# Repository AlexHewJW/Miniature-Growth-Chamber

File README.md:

# Miniature-Growth-Chamber
This is an electronics project that aims to create a miniaturised version of growth chamber to cultivate Arabidopsis under microscope under a long period of time. The problem reseachers have is the grow light that the plants need would interfere with some microscope such as the Raman microscope which is supposed to work without any surrounding light interference.

Hence, the project is aim-ed to create a 'light tight' microchamber that is small enough to fit under the microscope while also provide appropriate grow light to cultivate plants.

During my research, I've found out the LEDs would dissipate some heat that can be unconfortable for the plant, which leads me to create a novel solution prototype that uses fibre optic end glow light pipe to transfer light from remotely located LEDs.

Yet, I still continued my research on the original method of installing LEDs inside the growth chamber and found out that the heat dissipation isn't bad at all.

Here you would see 2 EAGLE files for PCB design, which are for both novel and original solution. 

The single AutoCAD file holds the microchamber design for both novel and original solution.

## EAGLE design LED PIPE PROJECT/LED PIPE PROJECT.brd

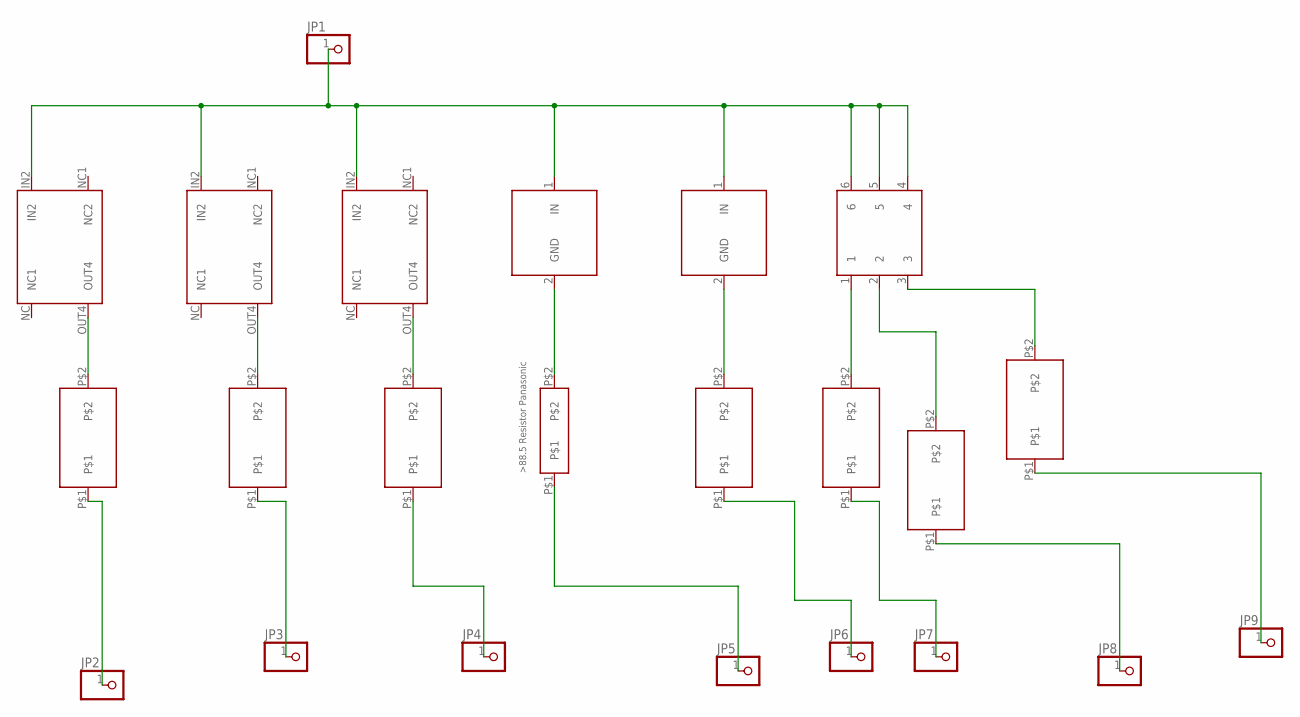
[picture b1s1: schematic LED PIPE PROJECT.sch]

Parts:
JP1, JP2, JP3, JP4, JP5, JP6, JP7, JP8, JP9: PINHD-1X1; 1X01
U$1: UV_LED
U$2: IR_LED
U$3: SMALL_RGB
U$4, U$5, U$6: SMALL_BRIGHT_COOL_WHITE
U$7, U$8, U$9, U$11, U$12, U$13, U$14: 68_60_56_RESISTOR_VISHAY
U$10: 88.5_RESISTOR_PANASONIC; 88.7_RESISTOR_PANASONIC

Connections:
unnamed: JP1.1, U$1.1 (IN), U$2.1 (IN), U$3.4, U$3.5, U$3.6, U$4.IN2, U$5.IN2, U$6.IN2
unnamed: U$6.OUT4, U$7.P$2
unnamed: U$5.OUT4, U$8.P$2
unnamed: U$4.OUT4, U$9.P$2
unnamed: U$1.2 (GND), U$10.P$2
unnamed: U$2.2 (GND), U$11.P$2
unnamed: U$3.1, U$12.P$2
unnamed: U$3.2, U$13.P$2
unnamed: U$3.3, U$14.P$2
unnamed: JP2.1, U$7.P$1
unnamed: JP3.1, U$8.P$1
unnamed: JP4.1, U$9.P$1
unnamed: JP5.1, U$10.P$1
unnamed: JP6.1, U$11.P$1
unnamed: JP7.1, U$12.P$1
unnamed: JP8.1, U$13.P$1
unnamed: JP9.1, U$14.P$1

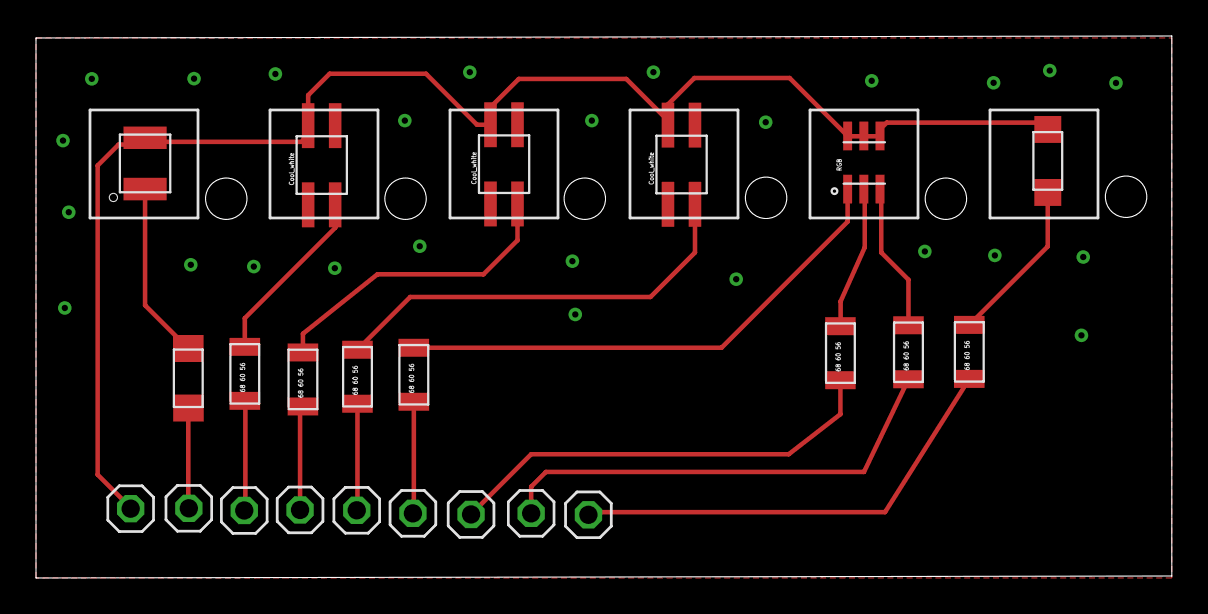
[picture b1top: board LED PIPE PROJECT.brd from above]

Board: 2 copper layers, 63.1 x 30.1 mm, 23 parts (0 on the bottom side), 17 nets.

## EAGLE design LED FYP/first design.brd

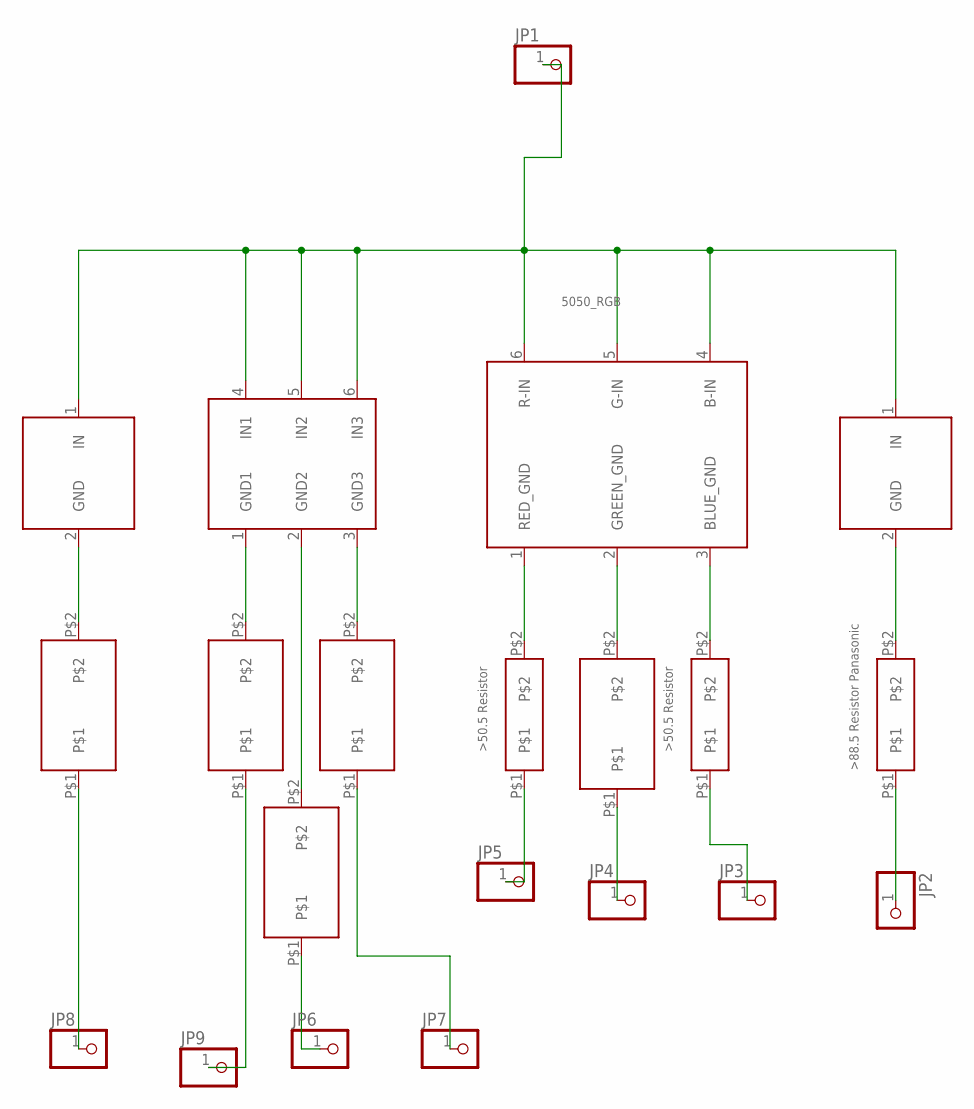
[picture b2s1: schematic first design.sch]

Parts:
JP1, JP2, JP3, JP4, JP5, JP6, JP7, JP8, JP9: PINHD-1X1; 1X01
U$1: 5.0X5.0_WHITE_LED; COOLWHITE5050LED
U$2: 5050_RGB_LED; RGB5050LED
U$3: IR_LED
U$4: UV_LED
U$5: 88.5_RESISTOR_PANASONIC; 88.7_RESISTOR_PANASONIC
U$6, U$7, U$8, U$9, U$12: 68_60_56_RESISTOR_VISHAY
U$10, U$11: 50.5_RESISTOR_TT

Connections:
unnamed: U$1.3 (GND3), U$9.P$2
unnamed: U$1.2 (GND2), U$8.P$2
unnamed: U$1.1 (GND1), U$7.P$2
unnamed: U$3.2 (GND), U$6.P$2
unnamed: U$2.1 (RED_GND), U$10.P$2
unnamed: U$2.2 (GREEN_GND), U$12.P$2
unnamed: U$2.3 (BLUE_GND), U$11.P$2
unnamed: U$4.2 (GND), U$5.P$2
unnamed: JP8.1, U$6.P$1
unnamed: JP9.1, U$7.P$1
unnamed: JP6.1, U$8.P$1
unnamed: JP1.1, U$1.4 (IN1), U$1.5 (IN2), U$1.6 (IN3), U$2.4 (B-IN), U$2.5 (G-IN), U$2.6 (R-IN), U$3.1 (IN), U$4.1 (IN)
unnamed: JP7.1, U$9.P$1
unnamed: JP5.1, U$10.P$1
unnamed: JP4.1, U$12.P$1
unnamed: JP3.1, U$11.P$1
unnamed: JP2.1, U$5.P$1

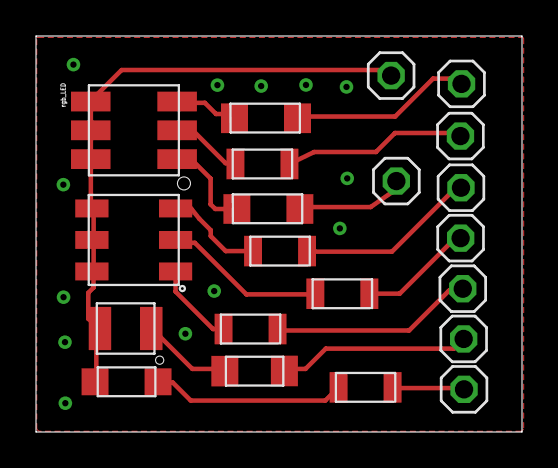
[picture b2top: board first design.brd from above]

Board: 2 copper layers, 27.0 x 22.0 mm, 21 parts (0 on the bottom side), 17 nets.

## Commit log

2022-10-10 temporary
